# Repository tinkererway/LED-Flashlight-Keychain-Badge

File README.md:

# LED-Flashlight-Keychain-Badge
Simple DIY (Do it yourself) PCB kit to learn soldering and electronics.

Project Details:https://tinkererway.com/2020/03/04/led-flash-light-badge/

Design Files: This project is designed using Open Source KiCad .Design files are located [here ](https://github.com/tinkererway/LED-Flashlight-Keychain-Badge/tree/master/Design%20files)

You can download Schematics from [here](https://github.com/tinkererway/LED-Flashlight-Keychain-Badge/tree/master/Schematics)

This work is licensed under the Creative Commons Attribution-ShareAlike 4.0 International (CC BY-SA 4.0). this license, visit https://creativecommons.org/licenses/by-sa/4.0/.

Made With ❤ in OpenSource

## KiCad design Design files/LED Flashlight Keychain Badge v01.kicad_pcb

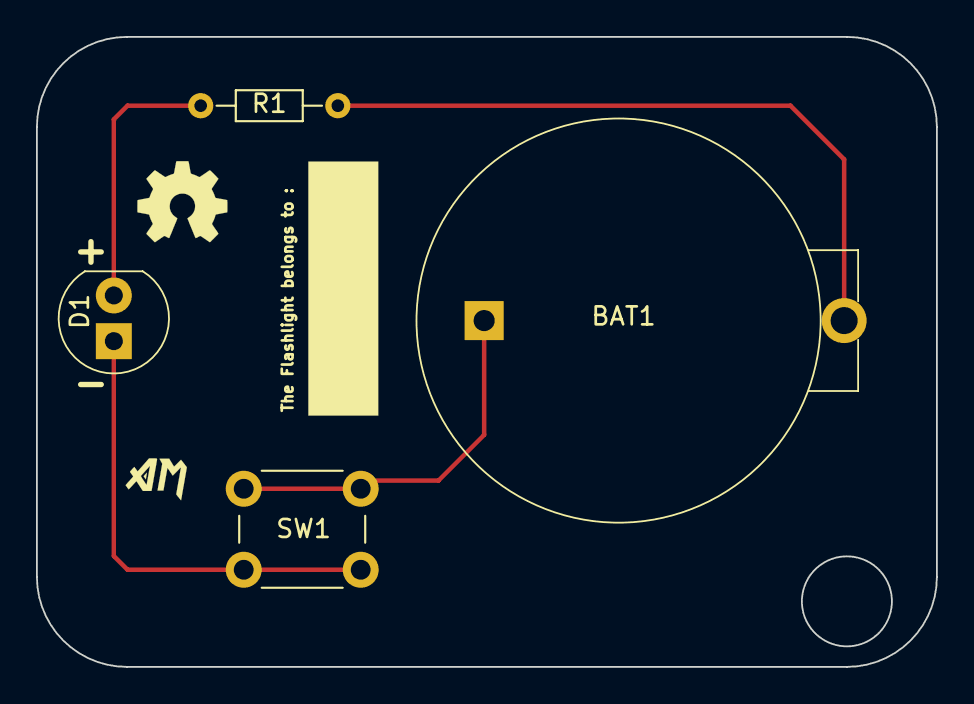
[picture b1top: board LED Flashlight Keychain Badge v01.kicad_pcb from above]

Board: 2 copper layers, 50.0 x 35.0 mm, 4 parts (0 on the bottom side), 4 nets.

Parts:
BAT1: Battery_Cell - CR2032; Battery_Holder_Coin_2032_BS-7-edited
D1: LED; LED_5mm_Radial
R1: 10; R_Axial_DIN0204_L3.6mm_D1.6mm_P7.62mm_Horizontal
SW1: SW_Push; SW_PUSH_6mm

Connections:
unnamed: BAT1.1, R1.2
unnamed: BAT1.2, SW1.2
unnamed: D1.1, SW1.1
unnamed: D1.2, R1.1
